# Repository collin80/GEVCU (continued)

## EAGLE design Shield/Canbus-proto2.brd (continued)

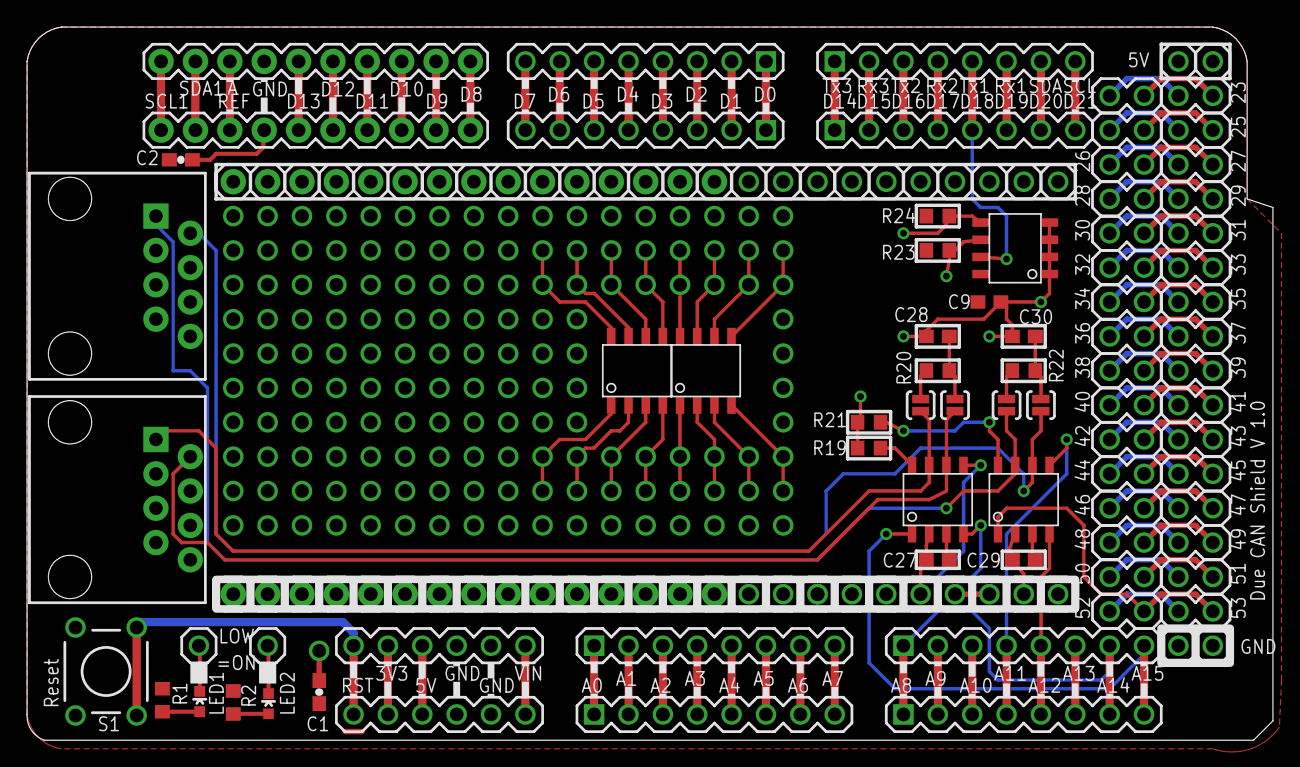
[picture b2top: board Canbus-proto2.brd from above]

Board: 2 copper layers, 92.1 x 52.7 mm, 81 parts (0 on the bottom side), 92 nets.

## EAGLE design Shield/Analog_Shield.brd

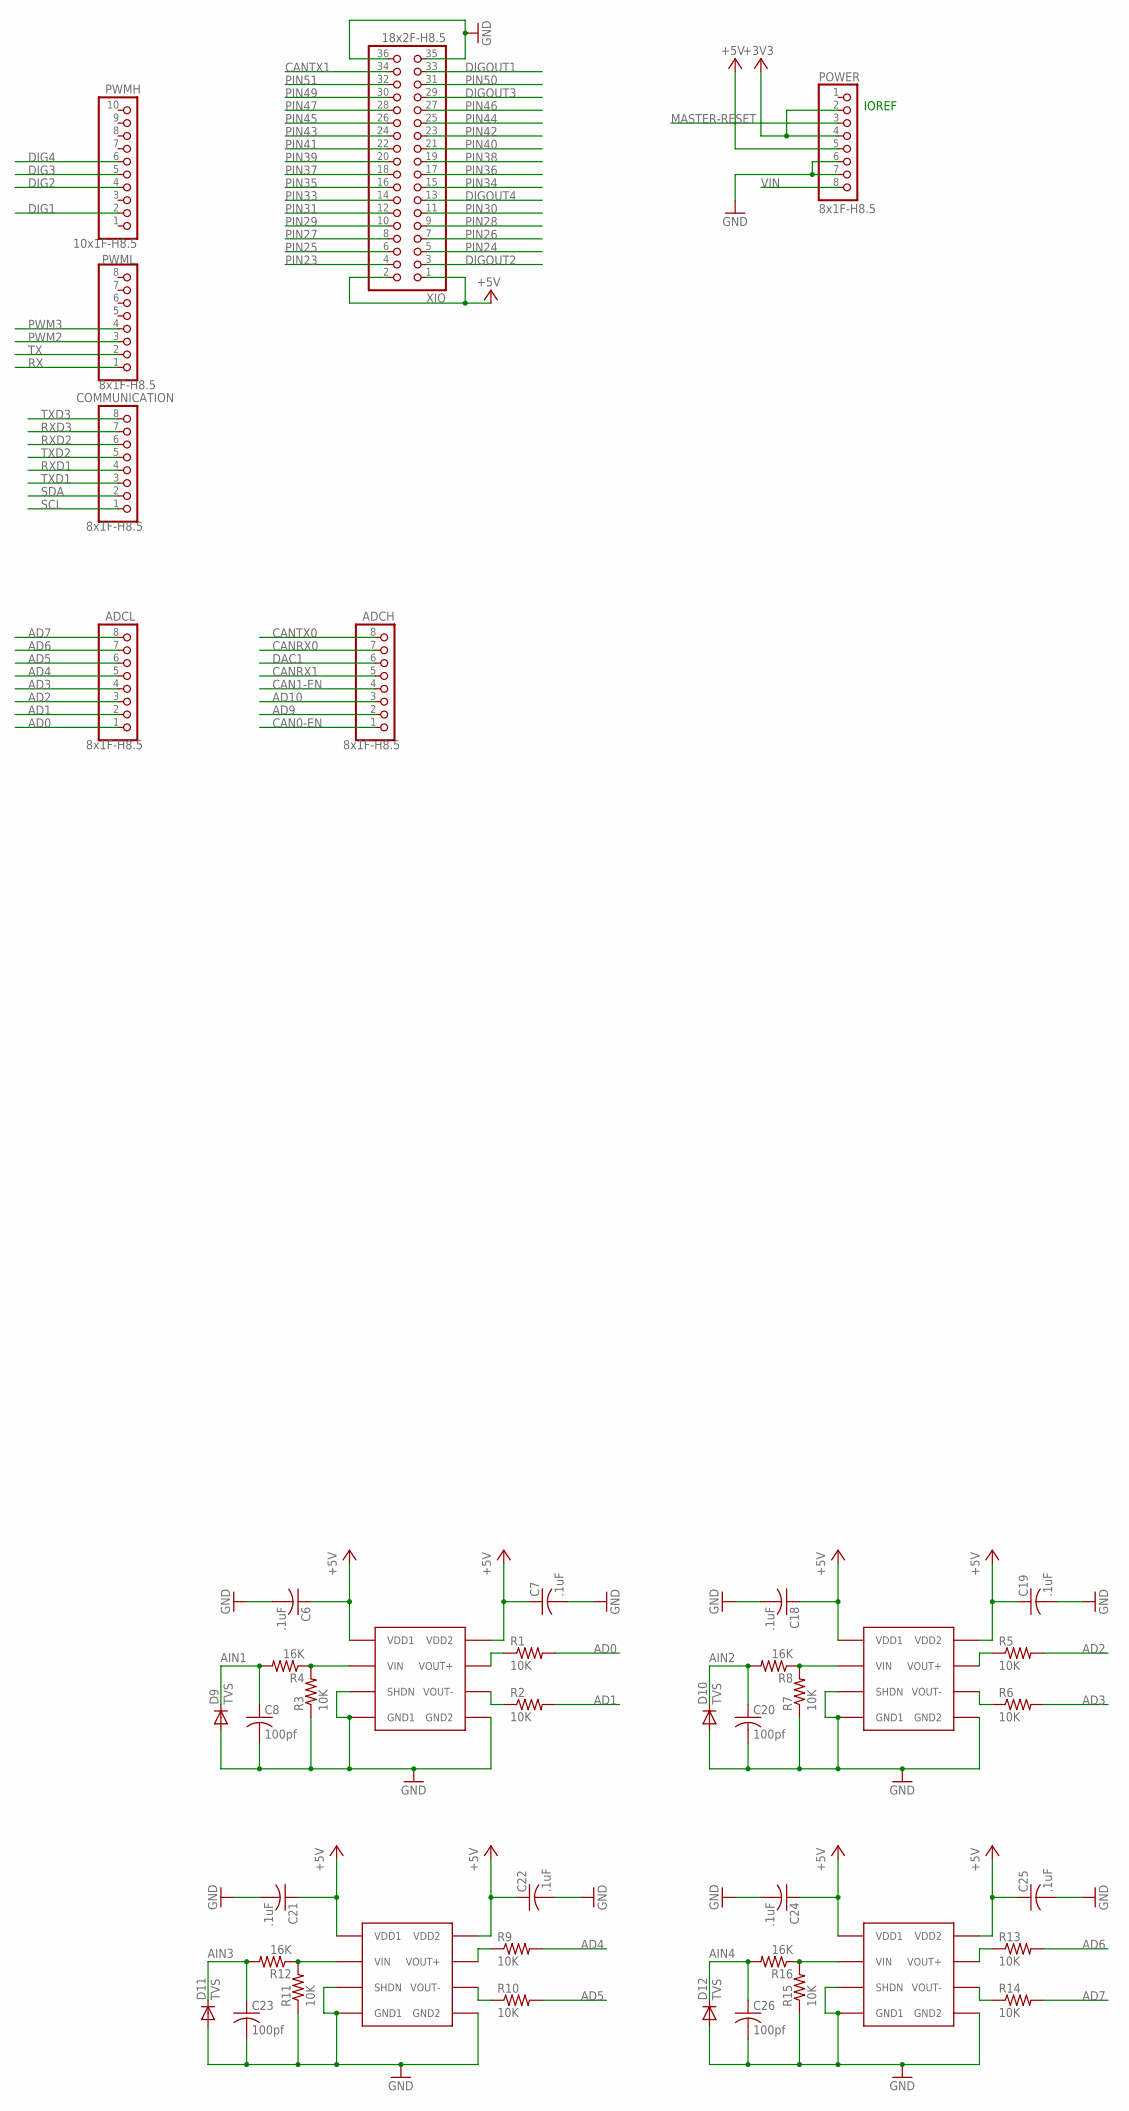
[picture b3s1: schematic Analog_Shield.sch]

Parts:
ADCH: 8x1F-H8.5; 1X08
ADCL: 8x1F-H8.5; 1X08
C6, C7, C18, C19, C21, C22, C24, C25: .1uF; C0603
C8, C20, C23, C26: 100pf; C0603
COMMUNICATION: 8x1F-H8.5; 1X08
D9, D10, D11, D12: TVS; SOD-323
POWER: 8x1F-H8.5; 1X08
PWMH: 10x1F-H8.5; 1X10
PWML: 8x1F-H8.5; 1X08
R1, R2, R3, R5, R6, R7, R9, R10, R11, R13, R14, R15: 10K; R0603
R4, R8, R12, R16: 16K; R0603
U$1, U$10, U$11, U$12: ACPL-C87A-000E; SO8-WIDE
XIO: 18x2F-H8.5; 2X18

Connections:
+3V3: POWER.2, POWER.4
+5V: C6.1, C7.1, C18.1, C19.1, C21.1, C22.1, C24.1, C25.1, POWER.5, U$1.1 (VDD1), U$1.8 (VDD2), U$10.1 (VDD1), U$10.8 (VDD2), U$11.1 (VDD1), U$11.8 (VDD2), U$12.1 (VDD1), U$12.8 (VDD2), XIO.1, XIO.2
AD0: ADCL.1, R1.2
AD1: ADCL.2, R2.2
AD2: ADCL.3, R5.2
AD3: ADCL.4, R6.2
AD4: ADCL.5, R9.2
AD5: ADCL.6, R10.2
AD6: ADCL.7, R13.2
AD7: ADCL.8, R14.2
AD9: ADCH.2
AD10: ADCH.3
AIN1: C8.1, D9.1 (C), R4.2
AIN2: C20.1, D10.1 (C), R8.2
AIN3: C23.1, D11.1 (C), R12.2
AIN4: C26.1, D12.1 (C), R16.2
CAN0-EN: ADCH.1
CAN1-EN: ADCH.4
CANRX0: ADCH.7
CANRX1: ADCH.5
CANTX0: ADCH.8
CANTX1: XIO.34
DAC1: ADCH.6
DIG1: PWMH.2
DIG2: PWMH.4
DIG3: PWMH.5
DIG4: PWMH.6
DIGOUT1: XIO.33
DIGOUT2: XIO.3
DIGOUT3: XIO.29
DIGOUT4: XIO.13
GND: C6.2, C7.2, C8.2, C18.2, C19.2, C20.2, C21.2, C22.2, C23.2, C24.2, C25.2, C26.2, D9.2 (A), D10.2 (A), D11.2 (A), D12.2 (A), POWER.6, POWER.7, R3.1, R7.1, R11.1, R15.1, U$1.3 (SHDN), U$1.4 (GND1), U$1.5 (GND2), U$10.3 (SHDN), U$10.4 (GND1), U$10.5 (GND2), U$11.3 (SHDN), U$11.4 (GND1), U$11.5 (GND2), U$12.3 (SHDN), U$12.4 (GND1), U$12.5 (GND2), XIO.35, XIO.36
MASTER-RESET: POWER.3
unnamed: R1.1, U$1.7 (VOUT+)
unnamed: R2.1, U$1.6 (VOUT-)
unnamed: R3.2, R4.1, U$1.2 (VIN)
unnamed: R7.2, R8.1, U$10.2 (VIN)
unnamed: R5.1, U$10.7 (VOUT+)
unnamed: R6.1, U$10.6 (VOUT-)
unnamed: R11.2, R12.1, U$11.2 (VIN)
unnamed: R9.1, U$11.7 (VOUT+)
unnamed: R10.1, U$11.6 (VOUT-)
unnamed: R15.2, R16.1, U$12.2 (VIN)
unnamed: R13.1, U$12.7 (VOUT+)
unnamed: R14.1, U$12.6 (VOUT-)
PIN23: XIO.4
PIN24: XIO.5
PIN25: XIO.6
PIN26: XIO.7
PIN27: XIO.8
PIN28: XIO.9
PIN29: XIO.10
PIN30: XIO.11
PIN31: XIO.12
PIN33: XIO.14
PIN34: XIO.15
PIN35: XIO.16
PIN36: XIO.17
PIN37: XIO.18
PIN38: XIO.19
PIN39: XIO.20
PIN40: XIO.21
PIN41: XIO.22
PIN42: XIO.23
PIN43: XIO.24
PIN44: XIO.25
PIN45: XIO.26
PIN46: XIO.27
PIN47: XIO.28
PIN49: XIO.30
PIN50: XIO.31
PIN51: XIO.32
PWM2: PWML.3
PWM3: PWML.4
RX: PWML.1
RXD1: COMMUNICATION.4
RXD2: COMMUNICATION.6
RXD3: COMMUNICATION.7
SCL: COMMUNICATION.1
SDA: COMMUNICATION.2
TX: PWML.2
TXD1: COMMUNICATION.3
TXD2: COMMUNICATION.5
TXD3: COMMUNICATION.8
VIN: POWER.8

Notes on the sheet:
IOREF

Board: 2 copper layers, 43 parts (0 on the bottom side), 27 nets, no tracks yet.

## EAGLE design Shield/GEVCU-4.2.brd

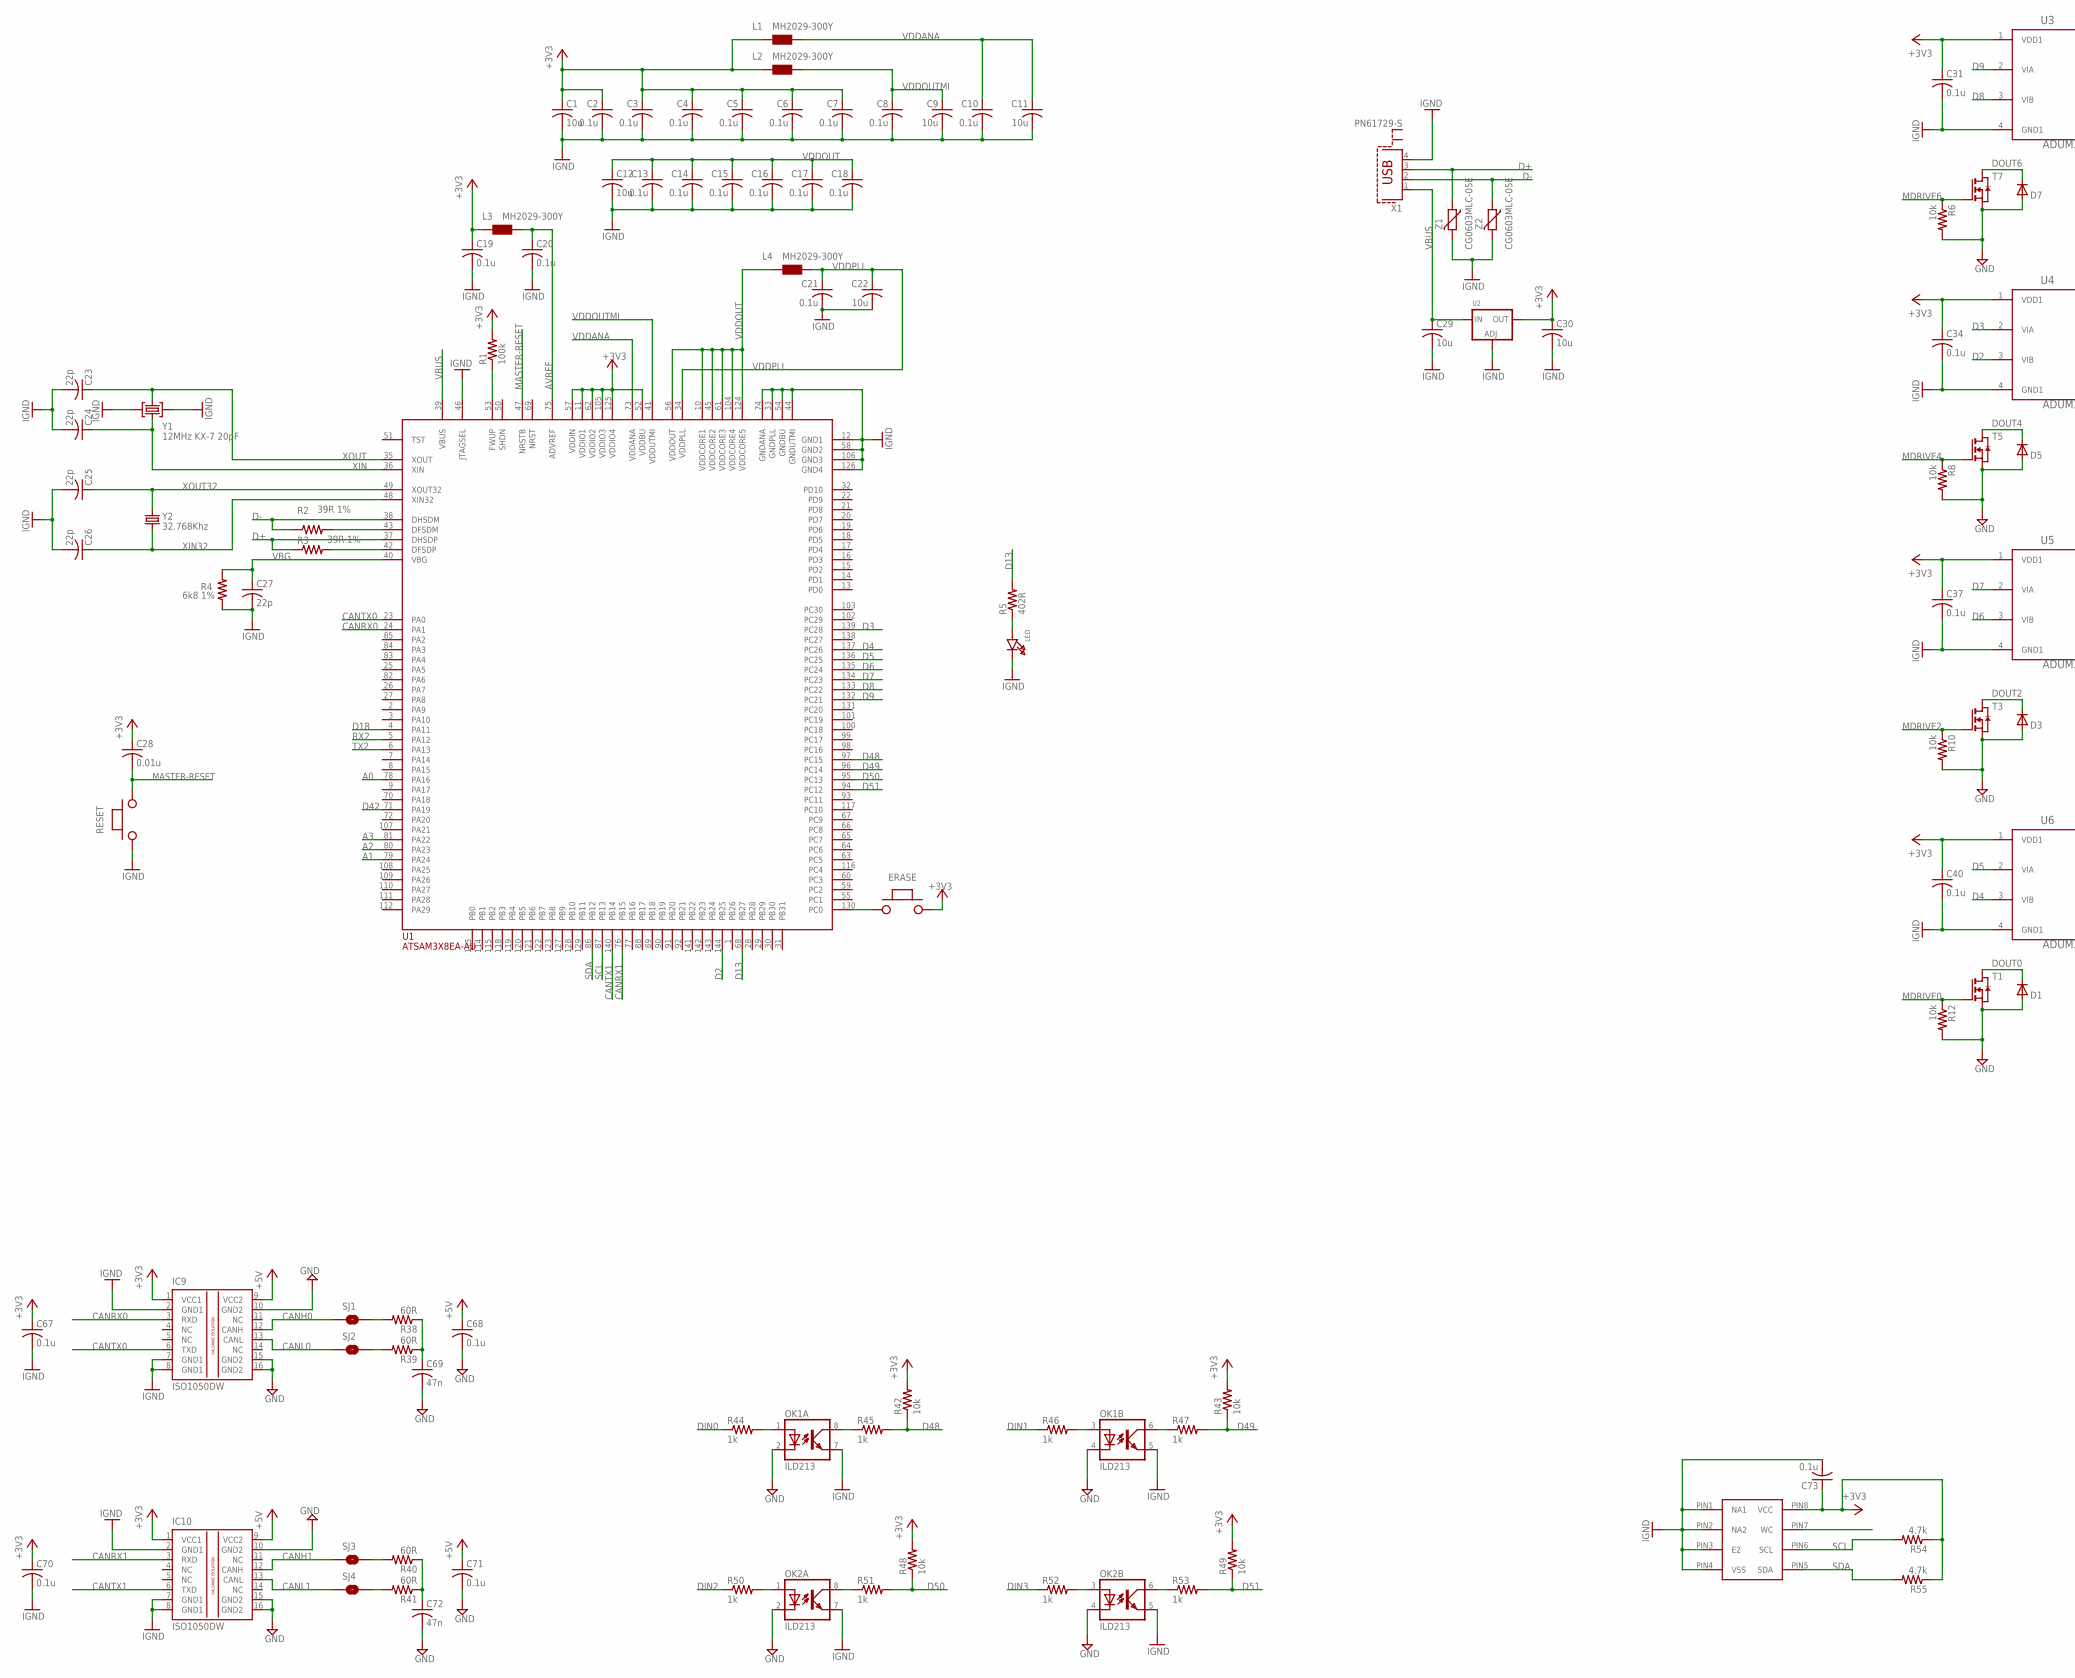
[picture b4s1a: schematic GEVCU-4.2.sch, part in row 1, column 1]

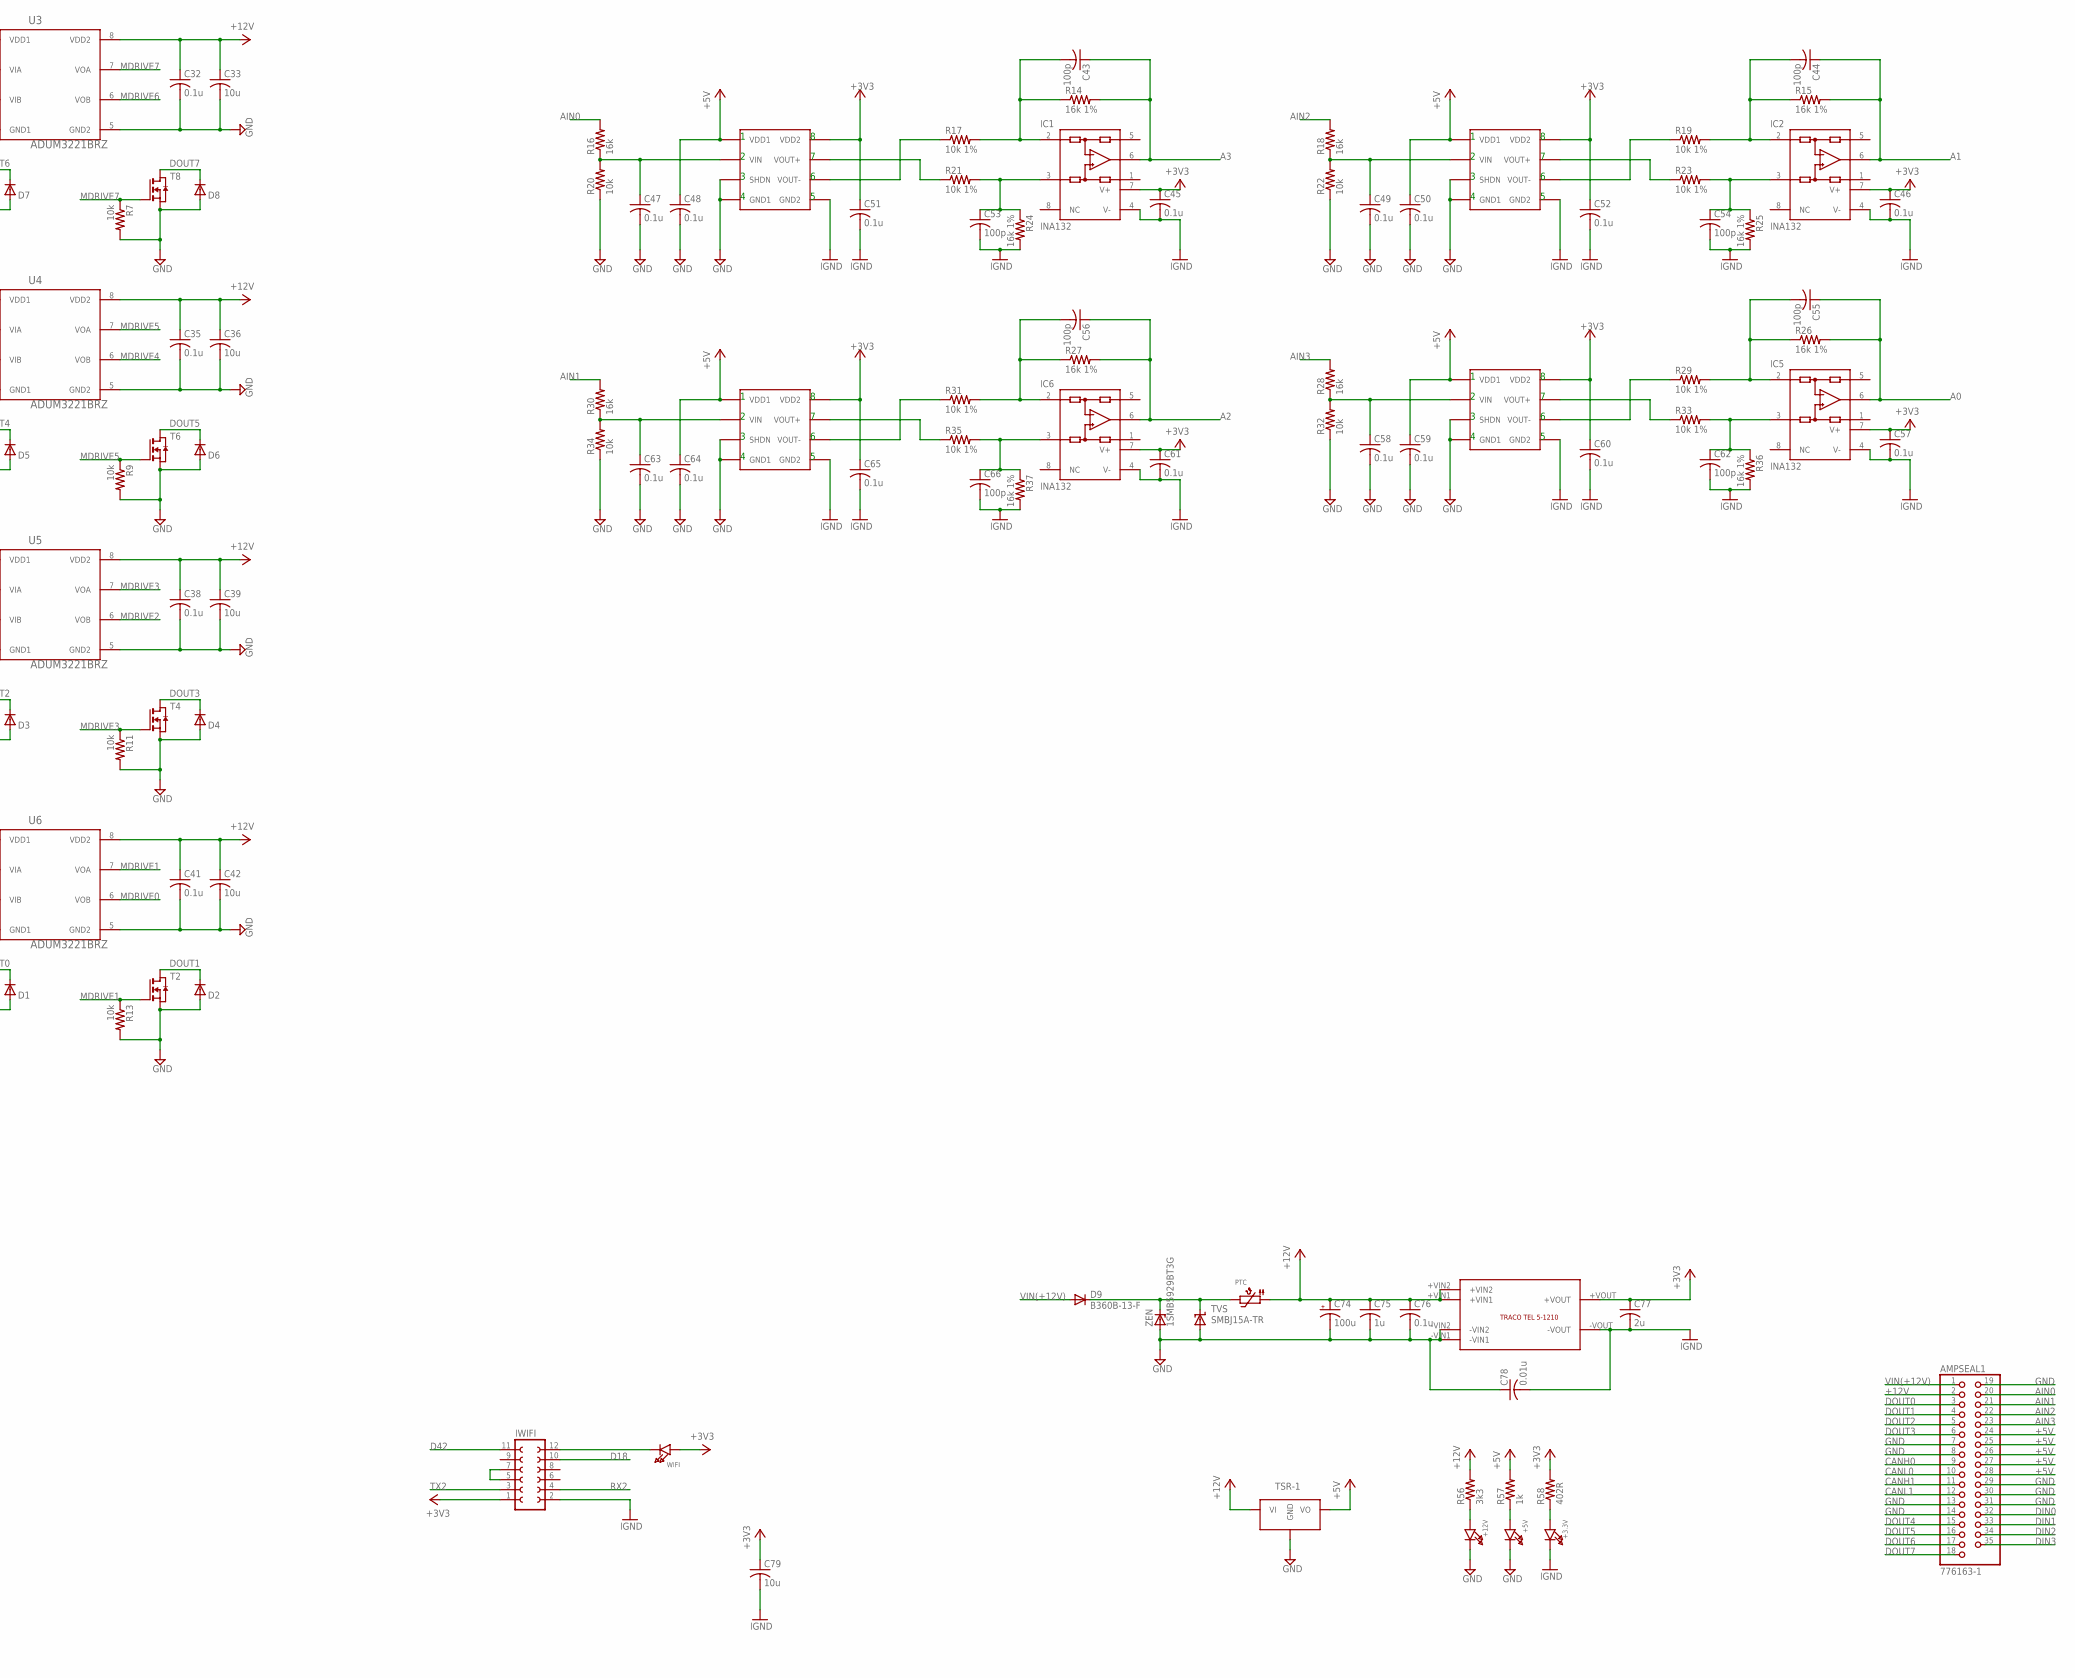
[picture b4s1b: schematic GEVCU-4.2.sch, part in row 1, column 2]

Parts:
+3.3V, +5V, +12V: LED0805; CHIPLED_0805
AMPSEAL1: 776163-1; AMPSEAL35
C1, C9, C11, C12, C22, C29, C30, C33, C36, C39, C42, C79: 10u; C0805
C2, C3, C4, C5, C6, C7, C8, C10, C13, C14, C15, C16, C17, C18, C19, C20, C21, C31, C32, C34, C35, C37, C38, C40, C41, C45, C46, C47, C49, C51, C52, C57, C58, C60, C61, C63, C65, C67, C68, C70, C71, C73, C76: 0.1u; C0805
C23, C24: 22p; C1206
C25, C26, C27: 22p; C0805
C28: 0.01u; C0805
C43, C44, C53, C54, C55, C56, C62, C66: 100p; C0805
C48, C50, C59, C64: 0.1u; C1206
C69, C72: 47n; C0805
C74: 100u; E2,5-6
C75: 1u; C0805
C77: 2u; C0805
C78: 0.01u; C1812
D1, D2, D3, D4, D5, D6, D7, D8: MBR0520LT; SOD123
D9: B360B-13-F; SMB
ERASE: PUCHBUTTON
IC1, IC2, IC5, IC6: INA132; SO08
IC3, IC4, IC7, IC8: CK_CUSTOM_ACPL-C87A-000E; CK_CUSTOM_SO8-WIDE
IC9, IC10: ISO1050DW; DUB-R-PDSO-G8
IWIFI: FE06-2
L1, L2, L3, L4: MH2029-300Y; 0805
LED: LED0805; CHIPLED_0805
OK1, OK2: ILD213; SOIC08
PTC: PTC1812
R1: 100k; R0805
R2, R3: 39R 1%; R0805
R4: 6k8 1%; R0805
R5, R58: 402R; R0805
R6, R7, R8, R9, R10, R11, R12, R13, R20, R22, R32, R34, R42, R43, R48, R49: 10k; R0805
R14, R15, R24, R25, R26, R27, R36, R37: 16k 1%; R0805
R16, R18, R28, R30: 16k; R0805
R17, R19, R21, R23, R29, R31, R33, R35: 10k 1%; R0805
R38, R39, R40, R41: 60R; R0805
R44, R45, R46, R47, R50, R51, R52, R53, R57: 1k; R0805
R54, R55: 4.7k; R0805
R56: 3k3; R0805
RESET: PUCHBUTTON
SJ1, SJ2, SJ3, SJ4: SOLDERJUMPERNO; SJ_2S-NO
T1, T2, T3, T4, T5, T6, T7, T8: NMOSSOT223; SOT223
TVS: SMBJ15A-TR; SMBJ
U1: ATSAM3X8EA-AU; LQFP144
U2: LM1117SOT223-WAVE; SOT223-W
U3, U4, U5, U6: ADUM3221BRZ; SOIC127P600X175-8N
U7: CK_CUSTOM_M24M02-DRMN6TP; CK_CUSTOM_SOIC8
U8: TRACO
U9: TSR-1
WIFI: LED0805; CHIPLED_0805
X1: PN61729-S
Y1: 12MHz KX-7 20pF; CRYSTAL-3.2-2.5
Y2: 32.768Khz; ARDUINO_WIFI_SHIELD_V018_TG_RESONATOR_EPSON_FC_145
Z1, Z2: CG0603MLC-05E; CT/CN0603
ZEN: 1SMB5929BT3G; SMB

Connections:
+3V3: C1.1, C2.1, C3.1, C4.1, C5.1, C6.1, C7.1, C19.1, C28.1, C30.1, C31.1, C34.1, C37.1, C40.1, C45.1, C46.1, C51.1, C52.1, C57.1, C60.1, C61.1, C65.1, C67.1, C70.1, C73.1, C77.1, C79.1, ERASE.P$2, IC1.7 (V+), IC2.7 (V+), IC3.8 (VDD2), IC4.8 (VDD2), IC5.7 (V+), IC6.7 (V+), IC7.8 (VDD2), IC8.8 (VDD2), IC9.1 (VCC1), IC10.1 (VCC1), IWIFI.1, L1.1, L2.1, L3.1, R1.2, R42.2, R43.2, R48.2, R49.2, R54.1, R55.1, R58.2, U1.11 (VDDIO1), U1.52 (VDDBU), U1.57 (VDDIN), U1.62 (VDDIO2), U1.105 (VDDIO3), U1.125 (VDDIO4), U2.2 (OUT), U3.1 (VDD1), U4.1 (VDD1), U5.1 (VDD1), U6.1 (VDD1), U7.PIN8 (VCC), U8.+VOUT, WIFI.A
+5V: AMPSEAL1.24, AMPSEAL1.25, AMPSEAL1.26, AMPSEAL1.27, AMPSEAL1.28, C48.1, C50.1, C59.1, C64.1, C68.1, C71.1, IC3.1 (VDD1), IC4.1 (VDD1), IC7.1 (VDD1), IC8.1 (VDD1), IC9.9 (VCC2), IC10.9 (VCC2), R57.2, U9.P$3 (VO)
+12V: AMPSEAL1.2, C32.1, C33.1, C35.1, C36.1, C38.1, C39.1, C41.1, C42.1, C74.+, C75.1, C76.1, PTC.P$1 (1), R56.2, U3.8 (VDD2), U4.8 (VDD2), U5.8 (VDD2), U6.8 (VDD2), U8.+VIN1, U8.+VIN2, U9.P$1 (VI)
A0: C55.1, IC5.6 (OUT), R26.2, U1.78 (PA16)
A1: C44.1, IC2.6 (OUT), R15.2, U1.79 (PA24)
A2: C56.1, IC6.6 (OUT), R27.2, U1.80 (PA23)
A3: C43.1, IC1.6 (OUT), R14.2, U1.81 (PA22)
AIN0: AMPSEAL1.20, R16.2
AIN1: AMPSEAL1.21, R30.2
AIN2: AMPSEAL1.22, R18.2
AIN3: AMPSEAL1.23, R28.2
AVREF: C20.1, L3.2, U1.75 (ADVREF)
CANH0: AMPSEAL1.9, IC9.12 (CANH), SJ1.1
CANH1: AMPSEAL1.11, IC10.12 (CANH), SJ3.1
CANL0: AMPSEAL1.10, IC9.13 (CANL), SJ2.1
CANL1: AMPSEAL1.12, IC10.13 (CANL), SJ4.1
CANRX0: IC9.3 (RXD), U1.24 (PA1)
CANRX1: IC10.3 (RXD), U1.76 (PB15)
CANTX0: IC9.6 (TXD), U1.23 (PA0)
CANTX1: IC10.6 (TXD), U1.140 (PB14)
D2: U1.144 (PB25), U4.3 (VIB)
D3: U1.139 (PC28), U4.2 (VIA)
D4: U1.137 (PC26), U6.3 (VIB)
D5: U1.136 (PC25), U6.2 (VIA)
D6: U1.135 (PC24), U5.3 (VIB)
D7: U1.134 (PC23), U5.2 (VIA)
D8: U1.133 (PC22), U3.3 (VIB)
D9: U1.132 (PC21), U3.2 (VIA)
D13: R5.2, U1.68 (PB27)
D18: IWIFI.10, U1.4 (PA11)
D42: IWIFI.11, U1.71 (PA19)
D48: R42.1, R45.2, U1.97 (PC15)
D49: R43.1, R47.2, U1.96 (PC14)
D50: R48.1, R51.2, U1.95 (PC13)
D51: R49.1, R53.2, U1.94 (PC12)
D+: R3.1, U1.37 (DHSDP), X1.3, Z1.1
D-: R2.1, U1.38 (DHSDM), X1.2, Z2.1
DIN0: AMPSEAL1.32, R44.1
DIN1: AMPSEAL1.33, R46.1
DIN2: AMPSEAL1.34, R50.1
DIN3: AMPSEAL1.35, R52.1
DOUT0: AMPSEAL1.3, D1.C, T1.2 (D), T1.4 (D)
DOUT1: AMPSEAL1.4, D2.C, T2.2 (D), T2.4 (D)
DOUT2: AMPSEAL1.5, D3.C, T3.2 (D), T3.4 (D)
DOUT3: AMPSEAL1.6, D4.C, T4.2 (D), T4.4 (D)
DOUT4: AMPSEAL1.15, D5.C, T5.2 (D), T5.4 (D)
DOUT5: AMPSEAL1.16, D6.C, T6.2 (D), T6.4 (D)
DOUT6: AMPSEAL1.17, D7.C, T7.2 (D), T7.4 (D)
DOUT7: AMPSEAL1.18, D8.C, T8.2 (D), T8.4 (D)
ERASE_S: ERASE.P$1, U1.130 (PC0)
GND: +5V.C, +12V.C, AMPSEAL1.7, AMPSEAL1.8, AMPSEAL1.13, AMPSEAL1.14, AMPSEAL1.19, AMPSEAL1.29, AMPSEAL1.30, AMPSEAL1.31, C32.2, C33.2, C35.2, C36.2, C38.2, C39.2, C41.2, C42.2, C47.2, C48.2, C49.2, C50.2, C58.2, C59.2, C63.2, C64.2, C68.2, C69.2, C71.2, C72.2, C74.-, C75.2, C76.2, C78.1, D1.A, D2.A, D3.A, D4.A, D5.A, D6.A, D7.A, D8.A, IC3.3 (SHDN), IC3.4 (GND1), IC4.3 (SHDN), IC4.4 (GND1), IC7.3 (SHDN), IC7.4 (GND1), IC8.3 (SHDN), IC8.4 (GND1), IC9.10 (GND2), IC9.15 (GND2), IC9.16 (GND2), IC10.10 (GND2), IC10.15 (GND2), IC10.16 (GND2), OK1.2 (C), OK1.4 (C), OK2.2 (C), OK2.4 (C), R6.2, R7.2, R8.2, R9.2, R10.2, R11.2, R12.2, R13.2, R20.1, R22.1, R32.1, R34.1, T1.3 (S), T2.3 (S), T3.3 (S), T4.3 (S), T5.3 (S), T6.3 (S), T7.3 (S), T8.3 (S), TVS.A, U3.5 (GND2), U4.5 (GND2), U5.5 (GND2), U6.5 (GND2), U8.-VIN1, U8.-VIN2, U9.P$2 (GND), ZEN.A
IGND: +3.3V.C, C1.2, C2.2, C3.2, C4.2, C5.2, C6.2, C7.2, C8.2, C9.2, C10.2, C11.2, C12.2, C13.2, C14.2, C15.2, C16.2, C17.2, C18.2, C19.2, C20.2, C21.2, C22.2, C23.2, C24.2, C25.2, C26.2, C27.2, C29.2, C30.2, C31.2, C34.2, C37.2, C40.2, C45.2, C46.2, C51.2, C52.2, C53.2, C54.2, C57.2, C60.2, C61.2, C62.2, C65.2, C66.2, C67.2, C70.2, C73.2, C77.2, C78.2, C79.2, IC1.4 (V-), IC2.4 (V-), IC3.5 (GND2), IC4.5 (GND2), IC5.4 (V-), IC6.4 (V-), IC7.5 (GND2), IC8.5 (GND2), IC9.2 (GND1), IC9.7 (GND1), IC9.8 (GND1), IC10.2 (GND1), IC10.7 (GND1), IC10.8 (GND1), IWIFI.2, LED.C, OK1.5 (EMIT), OK1.7 (EMIT), OK2.5 (EMIT), OK2.7 (EMIT), R4.1, R24.2, R25.2, R36.2, R37.2, RESET.P$1, U1.12 (GND1), U1.33 (GNDPLL), U1.44 (GNDUTMI), U1.46 (JTAGSEL), U1.54 (GNDBU), U1.58 (GND2), U1.74 (GNDANA), U1.106 (GND3), U1.126 (GND4), U2.1 (ADJ), U3.4 (GND1), U4.4 (GND1), U5.4 (GND1), U6.4 (GND1), U7.PIN1 (NA1), U7.PIN2 (NA2), U7.PIN3 (E2), U7.PIN4 (VSS), U8.-VOUT, X1.4, Y1.2 (GND), Y1.4 (GND), Z1.2, Z2.2
MASTER-RESET: C28.2, RESET.P$2, U1.47 (NRSTB)
MDRIVE0: R12.1, T1.1 (G), U6.6 (VOB)
MDRIVE1: R13.1, T2.1 (G), U6.7 (VOA)
MDRIVE2: R10.1, T3.1 (G), U5.6 (VOB)
MDRIVE3: R11.1, T4.1 (G), U5.7 (VOA)
MDRIVE4: R8.1, T5.1 (G), U4.6 (VOB)
MDRIVE5: R9.1, T6.1 (G), U4.7 (VOA)
MDRIVE6: R6.1, T7.1 (G), U3.6 (VOB)
MDRIVE7: R7.1, T8.1 (G), U3.7 (VOA)
unnamed: C47.1, IC3.2 (VIN), R16.1, R20.2
unnamed: +3.3V.A, R58.1
unnamed: D9.C, PTC.P$2 (2), TVS.C, ZEN.C
unnamed: +5V.A, R57.1
unnamed: LED.A, R5.1
unnamed: IC8.7 (VOUT+), R35.1
unnamed: IC8.6 (VOUT-), R31.1
unnamed: C56.2, IC6.2 (-IN), R27.1, R31.2
unnamed: IC3.7 (VOUT+), R21.1
unnamed: IC3.6 (VOUT-), R17.1
unnamed: C43.2, IC1.2 (-IN), R14.1, R17.2
unnamed: C53.1, IC1.3 (+IN), R21.2, R24.1
unnamed: C66.1, IC6.3 (+IN), R35.2, R37.1
unnamed: C63.1, IC8.2 (VIN), R30.1, R34.2
unnamed: IC4.7 (VOUT+), R23.1
unnamed: IC4.6 (VOUT-), R19.1
unnamed: C44.2, IC2.2 (-IN), R15.1, R19.2
unnamed: C54.1, IC2.3 (+IN), R23.2, R25.1
unnamed: C49.1, IC4.2 (VIN), R18.1, R22.2
unnamed: C69.1, R38.1, R39.1
unnamed: IC7.7 (VOUT+), R33.1
unnamed: R38.2, SJ1.2
unnamed: R39.2, SJ2.2
unnamed: R41.2, SJ4.2
unnamed: C72.1, R40.1, R41.1
unnamed: R40.2, SJ3.2
unnamed: OK1.1 (A), R44.2
unnamed: OK1.3 (A), R46.2
unnamed: OK1.8 (COL), R45.1
unnamed: OK1.6 (COL), R47.1
unnamed: IC7.6 (VOUT-), R29.1
unnamed: OK2.6 (COL), R53.1
unnamed: C55.2, IC5.2 (-IN), R26.1, R29.2
unnamed: OK2.8 (COL), R51.1
unnamed: C62.1, IC5.3 (+IN), R33.2, R36.1
unnamed: OK2.1 (A), R50.2
unnamed: C58.1, IC7.2 (VIN), R28.1, R32.2
unnamed: OK2.3 (A), R52.2
unnamed: +12V.A, R56.1
unnamed: IWIFI.12, WIFI.C
unnamed: IWIFI.5, IWIFI.7
unnamed: R2.2, U1.43 (DFSDM)
unnamed: R3.2, U1.42 (DFSDP)
unnamed: R1.1, U1.53 (FWUP)
RX2: IWIFI.4, U1.5 (PA12)
RXD1: U7.PIN7 (WC)
SCL: R54.2, U1.87 (PB13), U7.PIN6 (SCL)
SDA: R55.2, U1.86 (PB12), U7.PIN5 (SDA)
TX2: IWIFI.3, U1.6 (PA13)
VBG: C27.1, R4.2, U1.40 (VBG)
VBUS: C29.1, U1.39 (VBUS), U2.3 (IN), X1.1
VDDANA: C10.1, C11.1, L1.2, U1.73 (VDDANA)
VDDOUT: C12.1, C13.1, C14.1, C15.1, C16.1, C17.1, C18.1, L4.1, U1.10 (VDDCORE1), U1.45 (VDDCORE2), U1.56 (VDDOUT), U1.61 (VDDCORE3), U1.104 (VDDCORE4), U1.124 (VDDCORE5)
VDDOUTMI: C8.1, C9.1, L2.2, U1.41 (VDDUTMI)
VDDPLL: C21.1, C22.1, L4.2, U1.34 (VDDPLL)
VIN(+12V): AMPSEAL1.1, D9.A
XIN: C24.1, U1.36 (XIN), Y1.1 (C1)
XIN32: C26.1, U1.48 (XIN32), Y2.P$2 (2)
XOUT: C23.1, U1.35 (XOUT), Y1.3 (C2)
XOUT32: C25.1, U1.49 (XOUT32), Y2.P$1 (1)

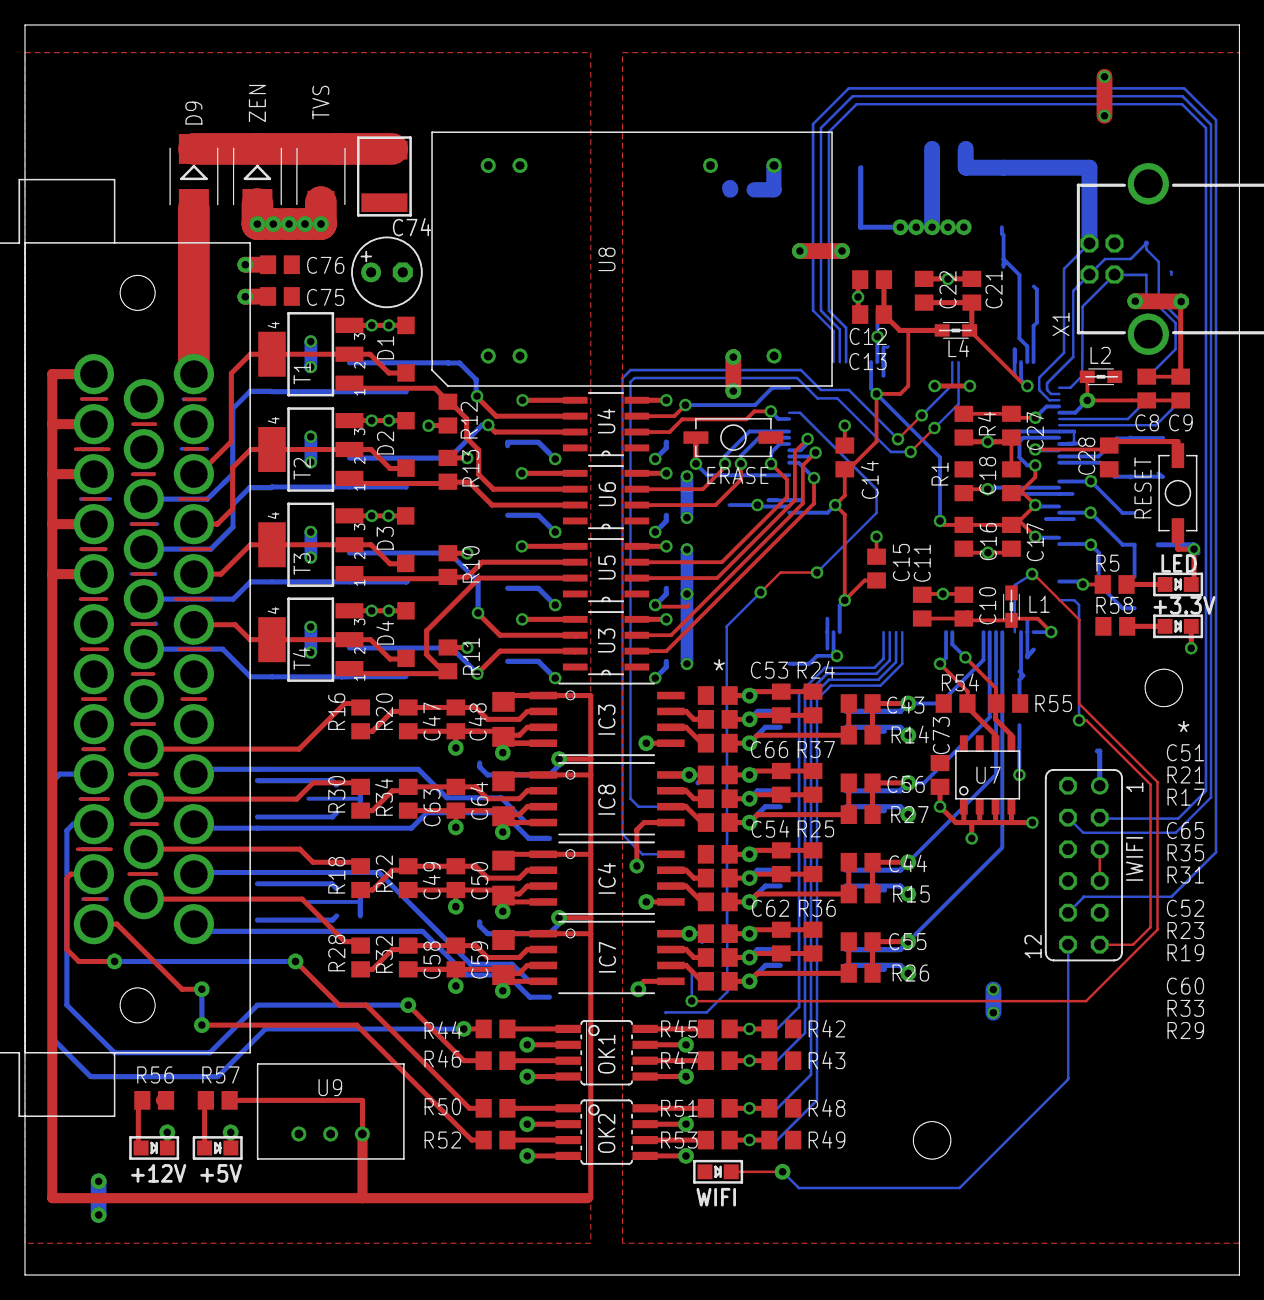
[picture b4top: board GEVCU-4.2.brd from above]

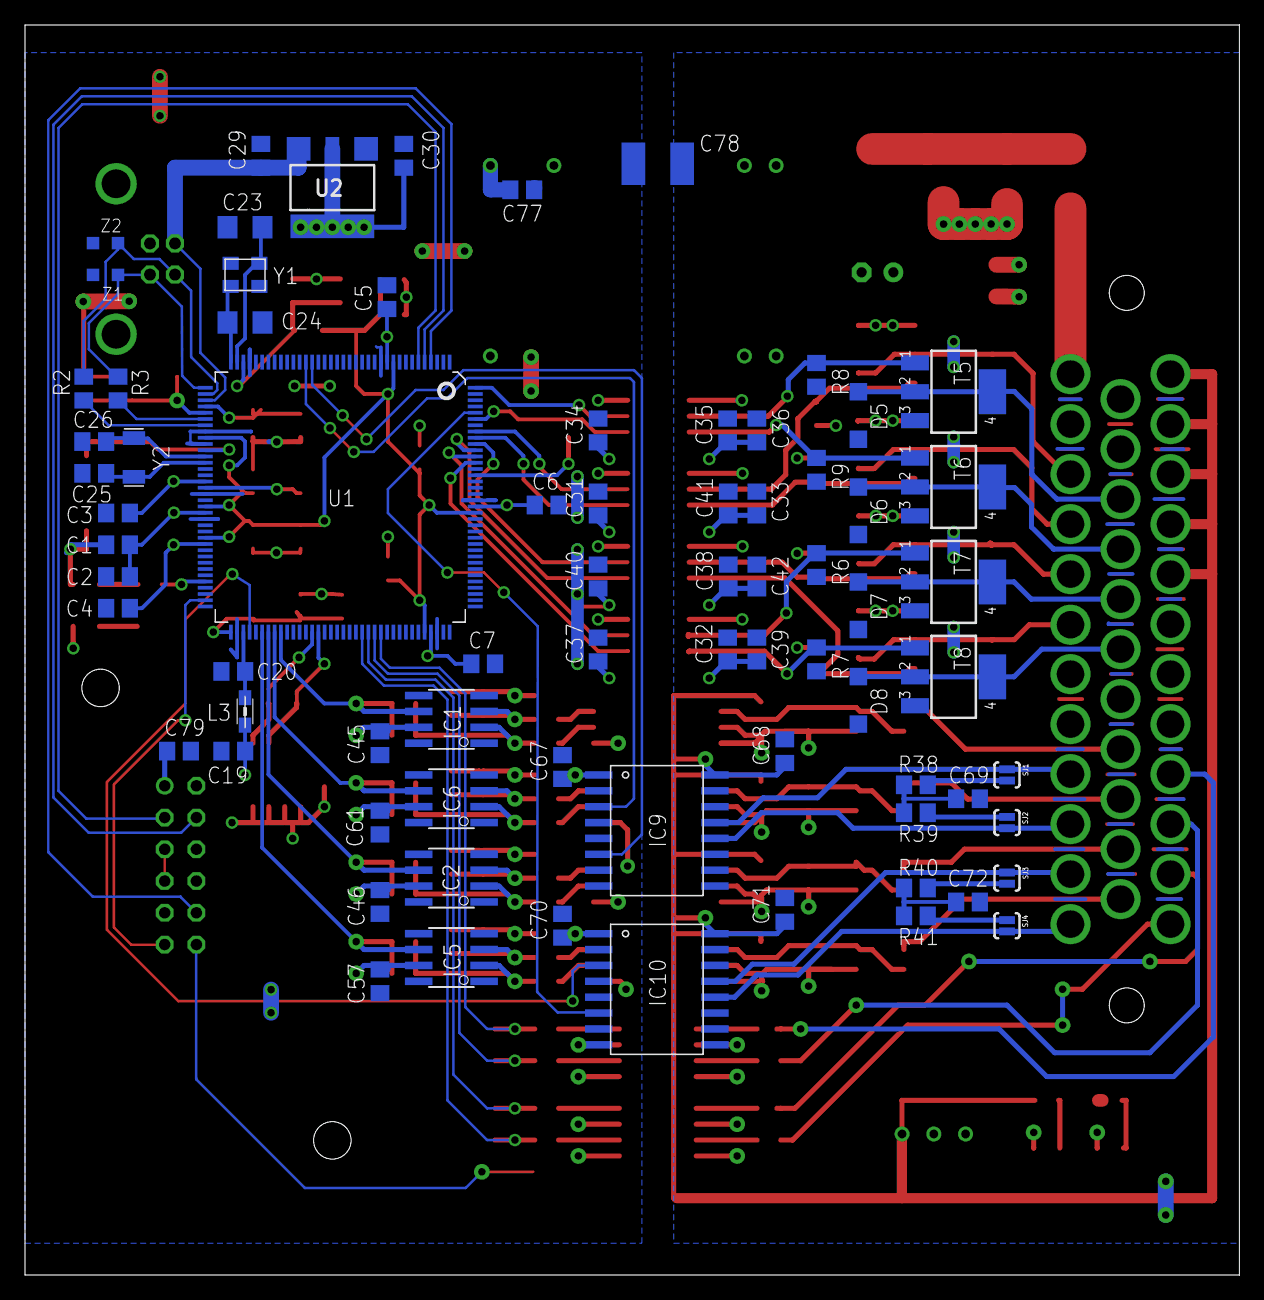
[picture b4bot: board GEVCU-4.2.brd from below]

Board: 2 copper layers, 97.2 x 100.0 mm, 200 parts (75 on the bottom side), 120 nets.
